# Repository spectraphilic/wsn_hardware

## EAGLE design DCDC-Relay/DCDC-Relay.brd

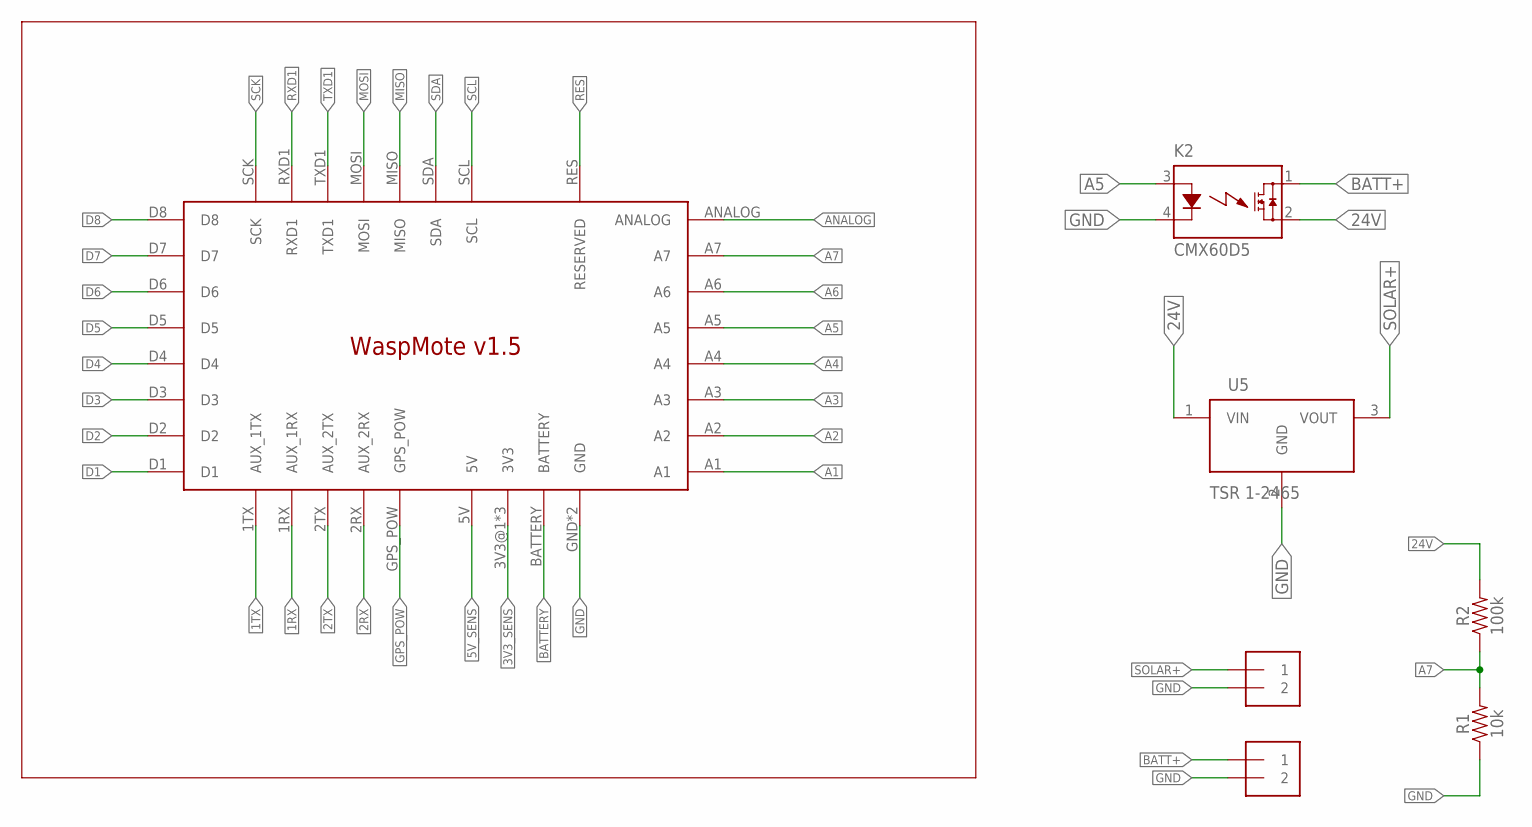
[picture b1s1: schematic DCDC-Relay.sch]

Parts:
J1, J2: 1X2-3.5MM
K2: CMX60D5
R1: 10k; AXIAL-0.3
R2: 100k; AXIAL-0.3
U5: TSR 1-2465; 173010535
U$1: WASPMOTE_V1.5

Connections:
1RX: U$1.1RX (AUX_1RX)
1TX: U$1.1TX (AUX_1TX)
2RX: U$1.2RX (AUX_2RX)
2TX: U$1.2TX (AUX_2TX)
3V3_SENS: U$1.3V3@1 (3V3), U$1.3V3@2 (3V3), U$1.3V3@3 (3V3)
5V_SENS: U$1.5V
24V: K2.2 (DS2), R2.P$2 (2), U5.1 (VIN)
A1: U$1.A1
A2: U$1.A2
A3: U$1.A3
A4: U$1.A4
A5: K2.3 (A), U$1.A5
A6: U$1.A6
A7: R1.P$2 (2), R2.P$1 (1), U$1.A7
ANALOG: U$1.ANALOG
BATT+: J1.1, K2.1 (DS1)
BATTERY: U$1.BATTERY
D1: U$1.D1
D2: U$1.D2
D3: U$1.D3
D4: U$1.D4
D5: U$1.D5
D6: U$1.D6
D7: U$1.D7
D8: U$1.D8
GND: J1.2, J2.2, K2.4 (K), R1.P$1 (1), U5.2 (GND), U$1.GND, U$1.GND_2 (GND)
GPS_POW: U$1.GPS_POW
MISO: U$1.MISO
MOSI: U$1.MOSI
RES: U$1.RES (RESERVED)
RXD1: U$1.RXD1
SCK: U$1.SCK
SCL: U$1.SCL
SDA: U$1.SDA
SOLAR+: J2.1, U5.3 (VOUT)
TXD1: U$1.TXD1

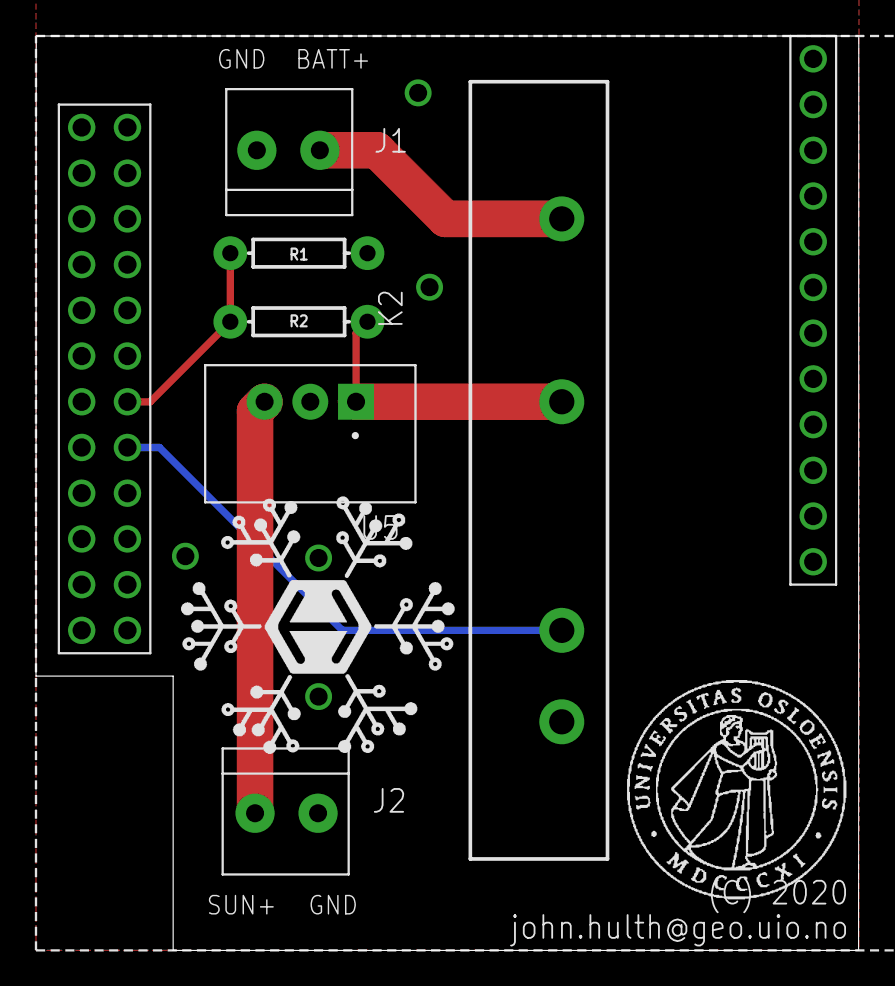
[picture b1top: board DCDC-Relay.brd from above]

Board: 2 copper layers, 45.7 x 50.8 mm, 9 parts (0 on the bottom side), 7 nets.

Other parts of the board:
U$2: HIVE-LOGO
U$3: UIO-LOGO-BL

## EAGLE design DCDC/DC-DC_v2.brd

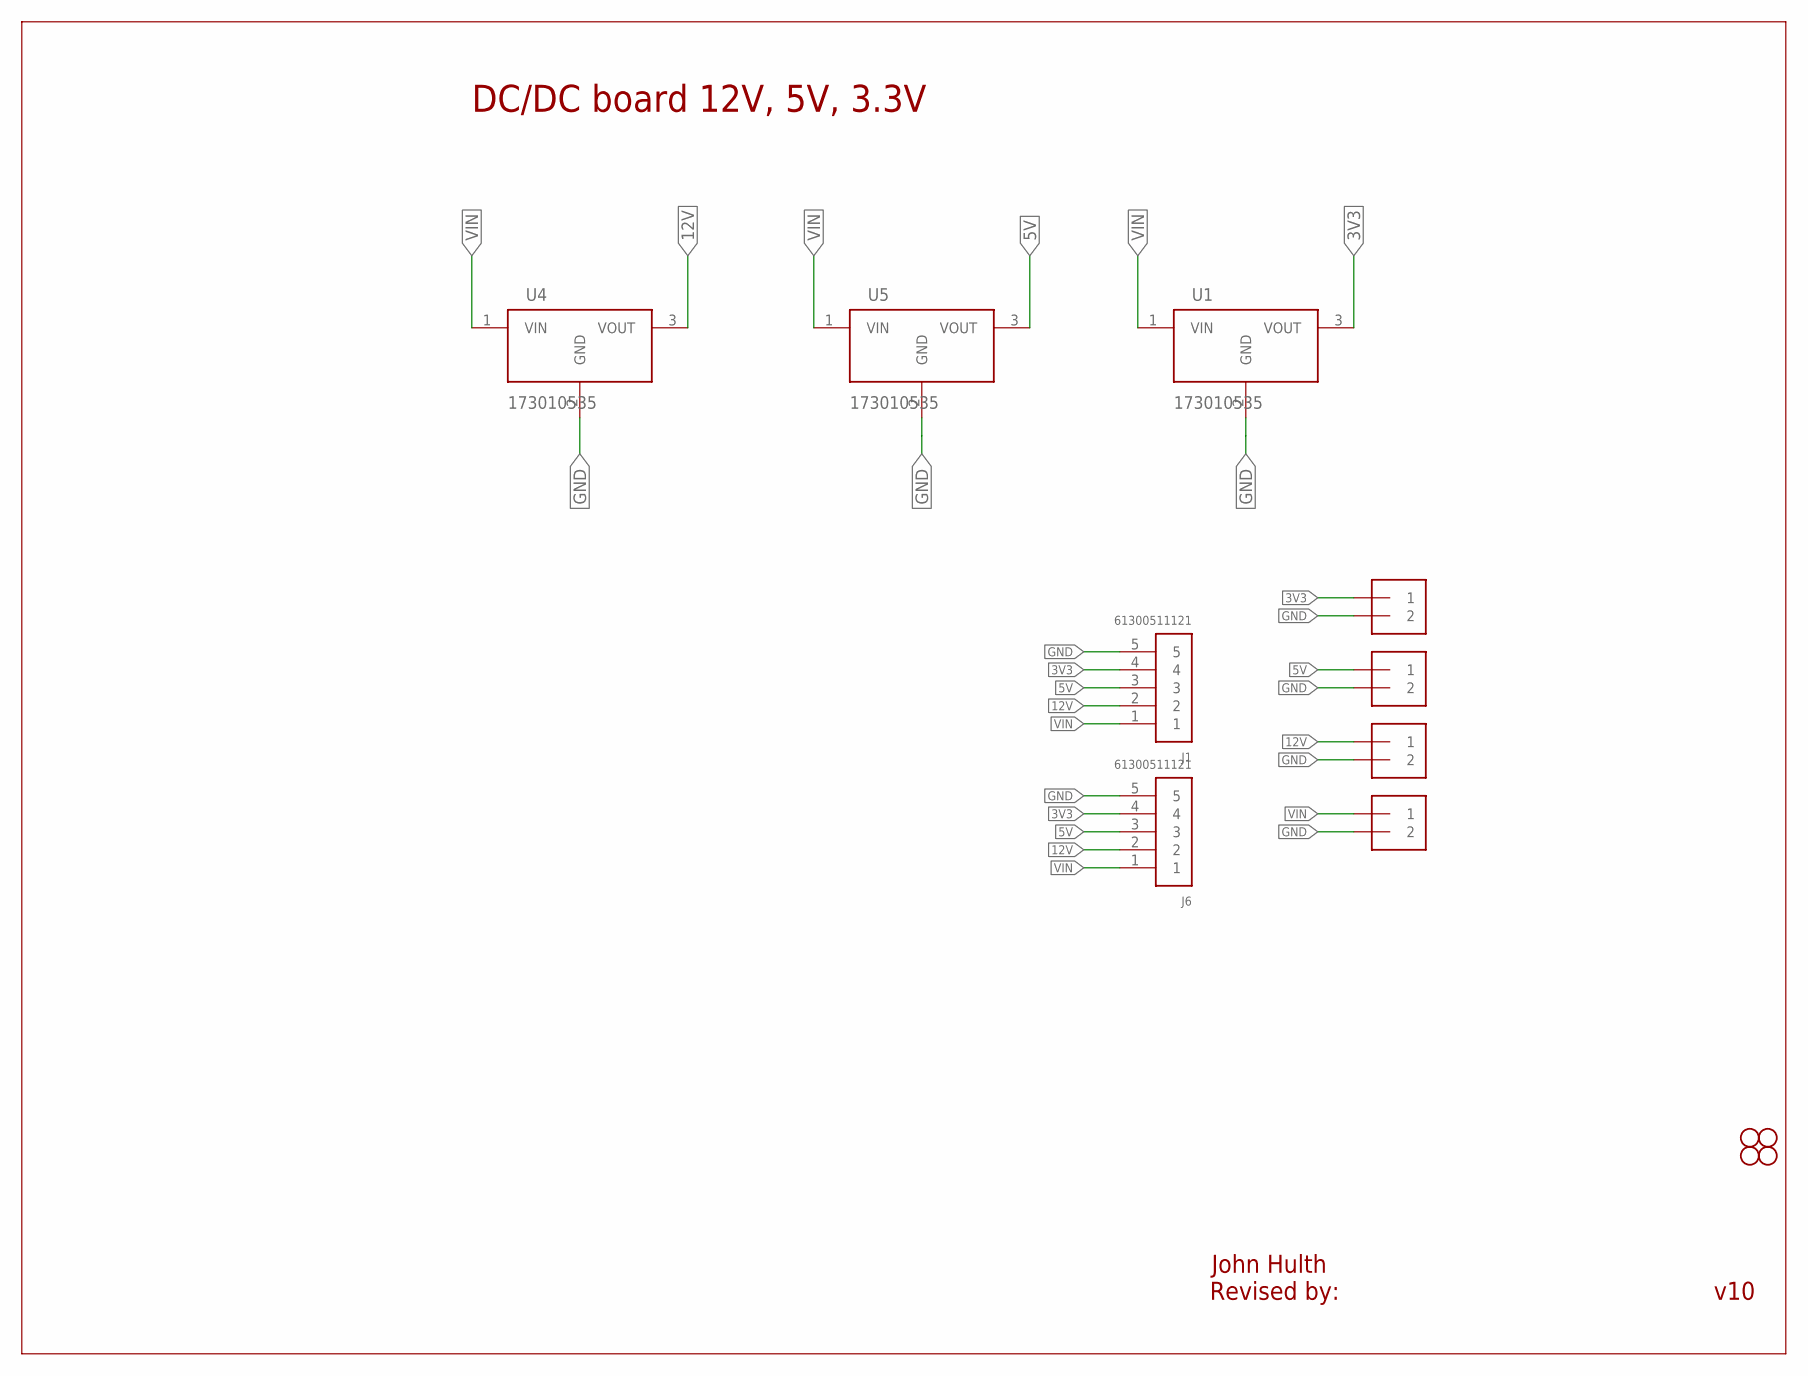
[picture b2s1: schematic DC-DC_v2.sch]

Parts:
J1, J6: 61300511121
J2, J3, J4, J5: 1X2-3.5MM
JP2, JP3, JP8, JP9: STAND-OFF
U1, U4, U5: 173010535

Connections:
3V3: J1.4, J2.1, J6.4, U1.3 (VOUT)
5V: J1.3, J3.1, J6.3, U5.3 (VOUT)
12V: J1.2, J4.1, J6.2, U4.3 (VOUT)
GND: J1.5, J2.2, J3.2, J4.2, J5.2, J6.5, U1.2 (GND), U4.2 (GND), U5.2 (GND)
VIN: J1.1, J5.1, J6.1, U1.1 (VIN), U4.1 (VIN), U5.1 (VIN)

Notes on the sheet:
DC/DC board 12V, 5V, 3.3V
John Hulth
v10
Revised by:

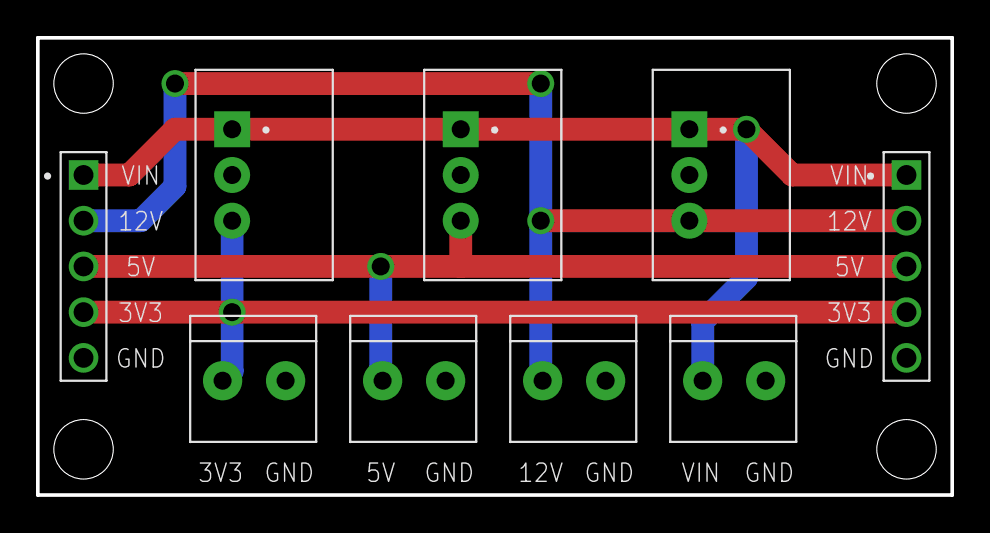
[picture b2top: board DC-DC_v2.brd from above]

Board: 2 copper layers, 50.8 x 25.4 mm, 14 parts (1 on the bottom side), 5 nets.

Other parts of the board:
U$3: UIO-LOGO-BL

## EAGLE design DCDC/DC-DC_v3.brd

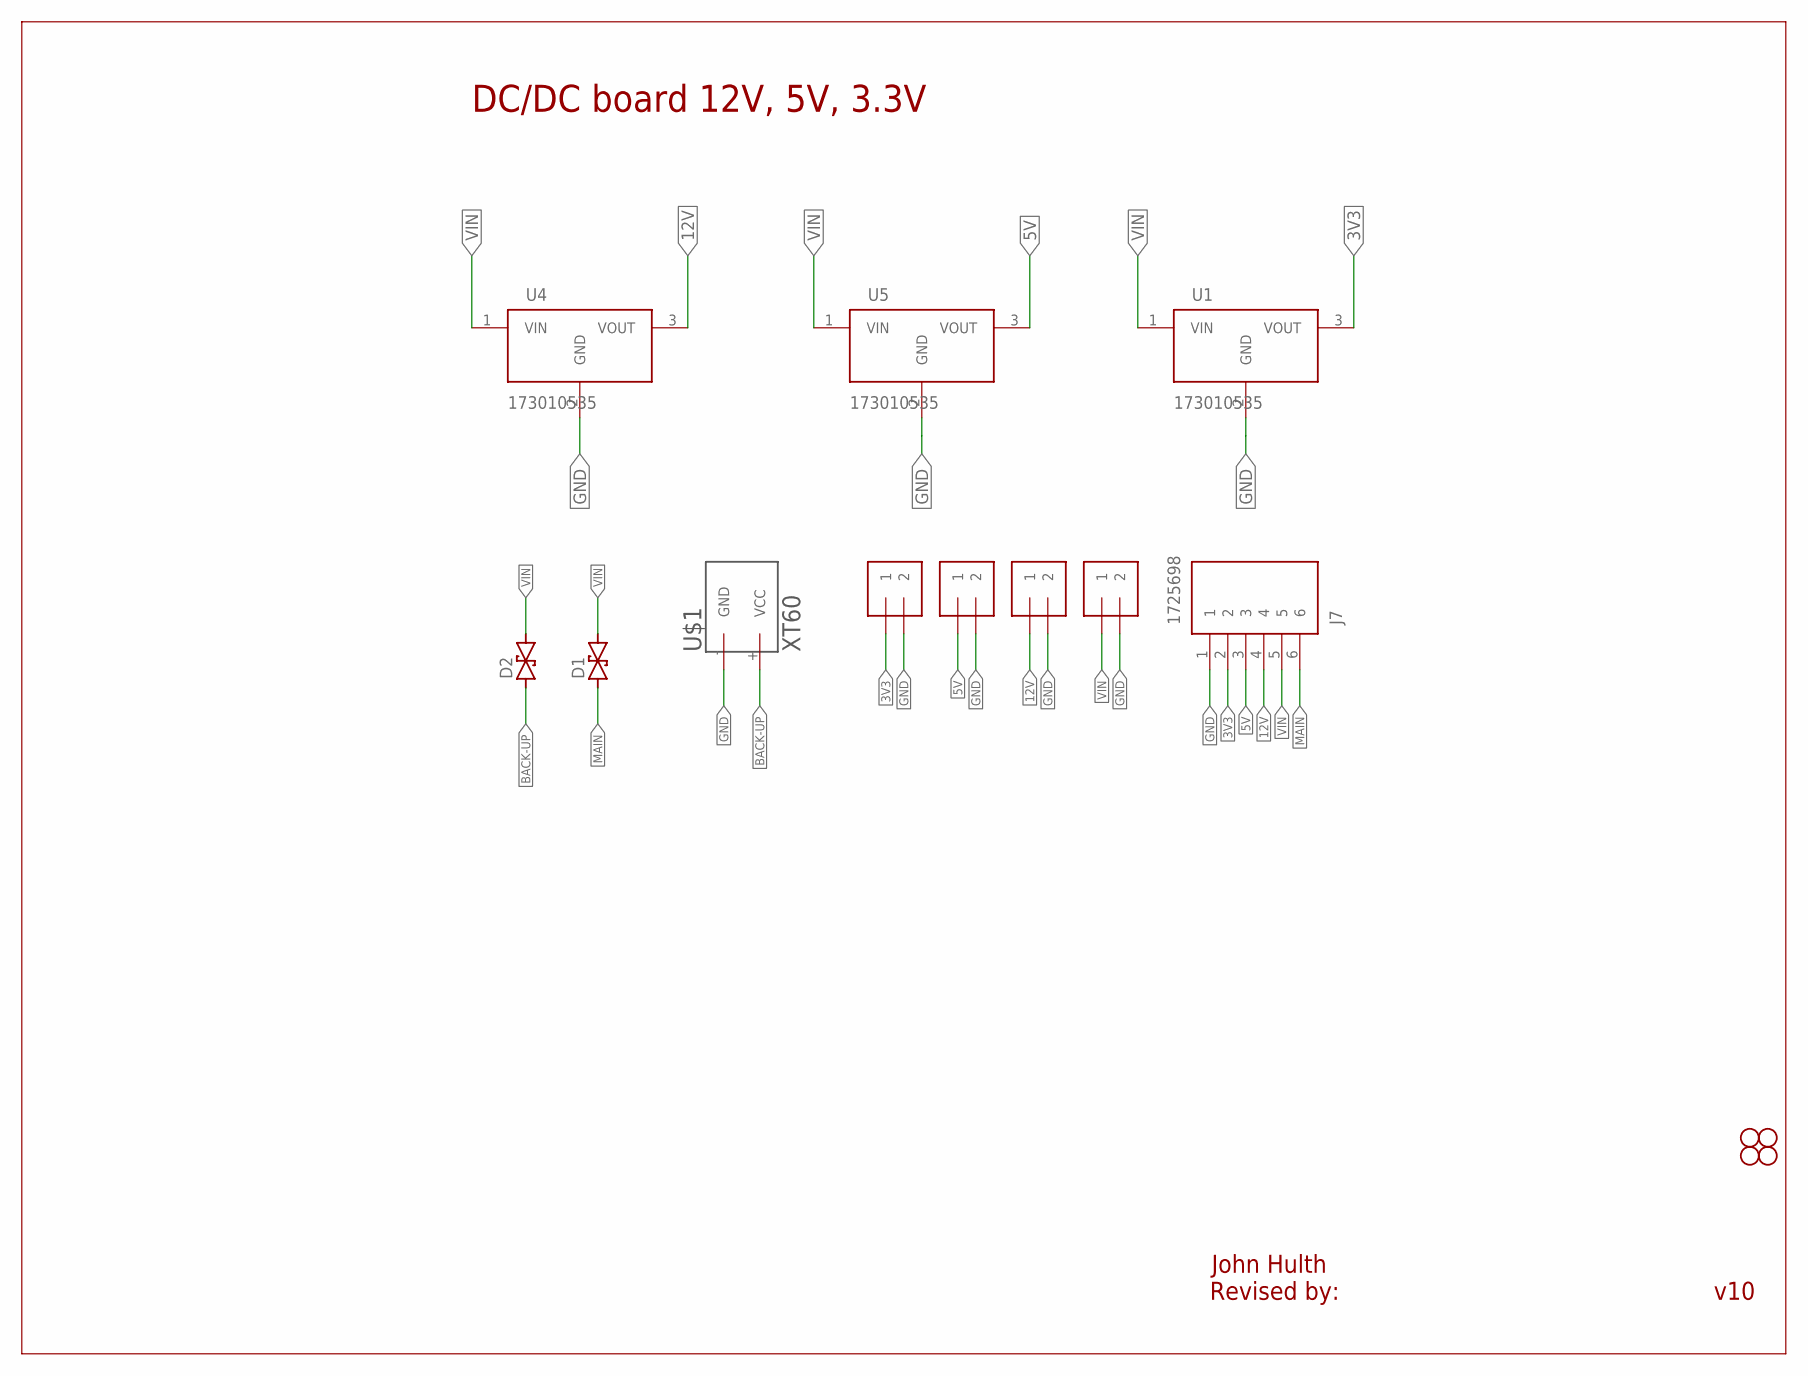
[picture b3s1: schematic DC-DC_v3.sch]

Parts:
D1, D2: DIODE_SCHOTTKY2-P2-15; P2-15
J2, J3, J4, J5: 1X2-3.5MM
J7: 1725698; SHDR6W90P0X254_1X6_1570X620X85
JP2, JP3, JP8, JP9: STAND-OFF
U1, U4, U5: 173010535
U$1: XT60

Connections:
3V3: J2.1, J7.2, U1.3 (VOUT)
5V: J3.1, J7.3, U5.3 (VOUT)
12V: J4.1, J7.4, U4.3 (VOUT)
BACK-UP: D2.A (1), U$1.+ (VCC)
GND: J2.2, J3.2, J4.2, J5.2, J7.1, U1.2 (GND), U4.2 (GND), U5.2 (GND), U$1.- (GND)
MAIN: D1.A (1), J7.6
VIN: D1.C (2), D2.C (2), J5.1, J7.5, U1.1 (VIN), U4.1 (VIN), U5.1 (VIN)

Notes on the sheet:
DC/DC board 12V, 5V, 3.3V
John Hulth
v10
Revised by:

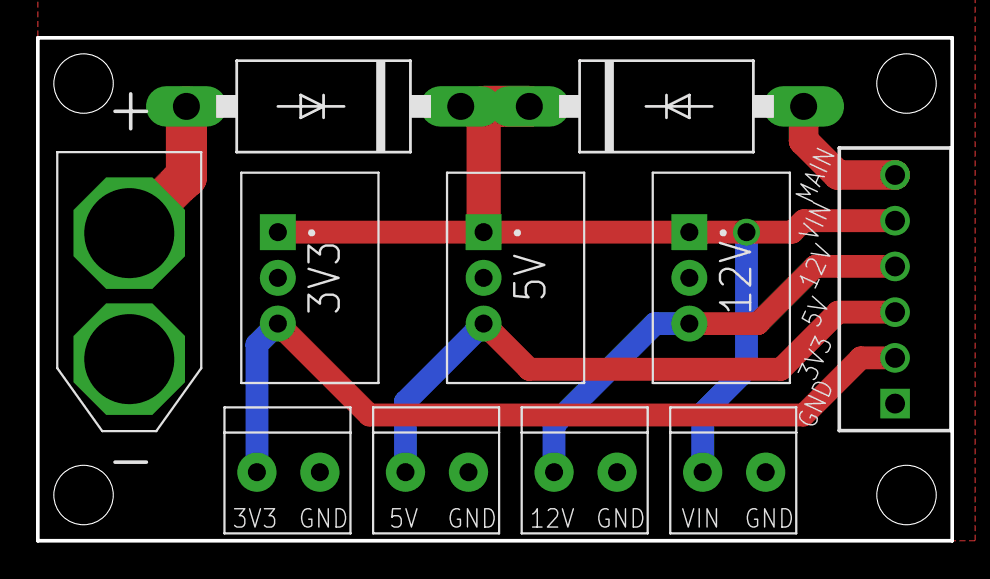
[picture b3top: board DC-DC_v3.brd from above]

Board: 2 copper layers, 50.8 x 27.9 mm, 16 parts (1 on the bottom side), 7 nets.

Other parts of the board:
U$3: UIO-LOGO-BL

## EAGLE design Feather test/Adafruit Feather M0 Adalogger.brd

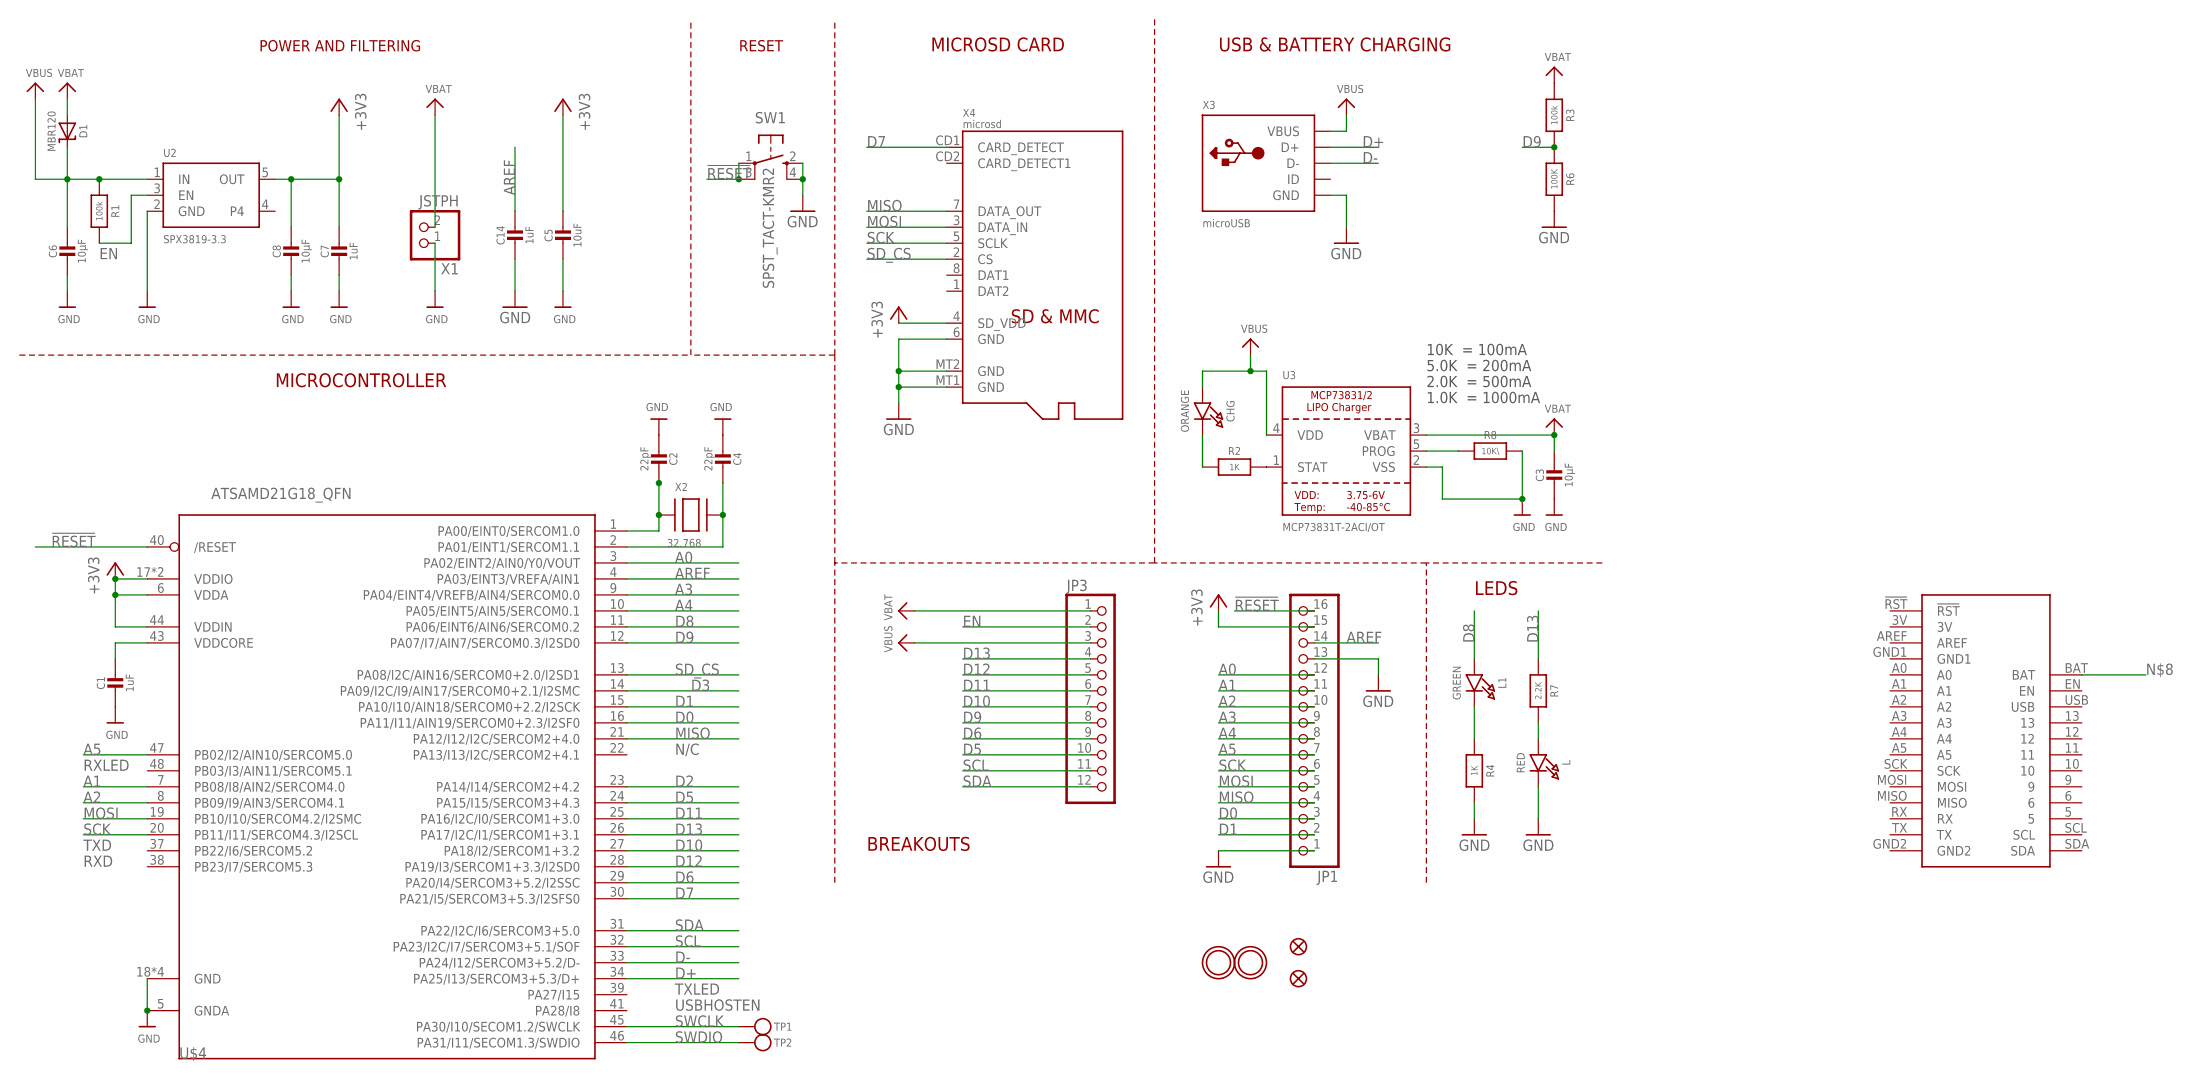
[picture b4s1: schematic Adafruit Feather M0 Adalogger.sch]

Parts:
C1, C7, C14: 1uF; 0603-NO
C2, C4: 22pF; 0603-NO
C3, C6, C8: 10µF; 0805-NO
C5: 10uF; 0805-NO
CHG: ORANGE; CHIPLED_0805_NOOUTLINE
D1: MBR120; SOD-123
JP1: HEADER-1X16ROUND; 1X16_ROUND
JP3: HEADER-1X12; 1X12_ROUND
L: RED; CHIPLED_0805_NOOUTLINE
L1: GREEN; CHIPLED_0805_NOOUTLINE
R1, R3: 100k; 0603-NO
R2, R4: 1K; 0603-NO
R6: 100K; 0603-NO
R7: 2.2K; 0603-NO
R8: 10K\; 0603-NO
SW1: SPST_TACT-KMR2; KMR2
TP1, TP2: TESTPOINTROUND1.5MM; TESTPOINT_ROUND_1.5MM
U2: SPX3819-3.3; SOT23-5
U3: MCP73831T-2ACI/OT; SOT23-5
U$4: ATSAMD21G18_QFN; TQFN48_7MM
U$12: FEATHER_MO_ADALOGGER; FEATHER_M0_ADALOGGER
U$31, U$32: MOUNTINGHOLE2.5; MOUNTINGHOLE_2.5_PLATED
U$34, U$35: FIDUCIAL""; FIDUCIAL_1MM
X1: JSTPH; JSTPH2
X2: 32.768; XTAL3215
X3: microUSB; 4UCONN_20329_V2
X4: microsd; MICROSD

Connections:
!RESET: JP1.16, SW1.1, SW1.3 (P1), U$4.40 (/RESET)
+3V3: C5.1, C7.1, C8.1, JP1.15, U2.5 (OUT), U$4.6 (VDDA), U$4.17 (VDDIO), U$4.36 (VDDIO), U$4.44 (VDDIN), X4.4 (SD_VDD)
A0: JP1.12, U$4.3 (PA02/EINT2/AIN0/Y0/VOUT)
A1: JP1.11, U$4.7 (PB08/I8/AIN2/SERCOM4.0)
A2: JP1.10, U$4.8 (PB09/I9/AIN3/SERCOM4.1)
A3: JP1.9, U$4.9 (PA04/EINT4/VREFB/AIN4/SERCOM0.0)
A4: JP1.8, U$4.10 (PA05/EINT5/AIN5/SERCOM0.1)
A5: JP1.7, U$4.47 (PB02/I2/AIN10/SERCOM5.0)
AREF: C14.1, JP1.14, U$4.4 (PA03/EINT3/VREFA/AIN1)
D0: JP1.3, U$4.16 (PA11/I11/AIN19/SERCOM0+2.3/I2SF0)
D1: JP1.2, U$4.15 (PA10/I10/AIN18/SERCOM0+2.2/I2SCK)
D2: U$4.23 (PA14/I14/SERCOM2+4.2)
D3: U$4.14 (PA09/I2C/I9/AIN17/SERCOM0+2.1/I2SMC)
D5: JP3.10, U$4.24 (PA15/I15/SERCOM3+4.3)
D6: JP3.9, U$4.29 (PA20/I4/SERCOM3+5.2/I2SSC)
D7: U$4.30 (PA21/I5/SERCOM3+5.3/I2SFS0), X4.CD1 (CARD_DETECT)
D8: L1.A, U$4.11 (PA06/EINT6/AIN6/SERCOM0.2)
D9: JP3.8, R3.2, R6.1, U$4.12 (PA07/I7/AIN7/SERCOM0.3/I2SD0)
D10: JP3.7, U$4.27 (PA18/I2/SERCOM1+3.2)
D11: JP3.6, U$4.25 (PA16/I2C/I0/SERCOM1+3.0)
D12: JP3.5, U$4.28 (PA19/I3/SERCOM1+3.3/I2SD0)
D13: JP3.4, R7.1, U$4.26 (PA17/I2C/I1/SERCOM1+3.1)
D+: U$4.34 (PA25/I13/SERCOM3+5.3/D+), X3.D+
D-: U$4.33 (PA24/I12/SERCOM3+5.2/D-), X3.D-
EN: JP3.2, R1.2, U2.3 (EN)
GND: C1.2, C2.2, C3.2, C4.2, C5.2, C6.2, C7.2, C8.2, C14.2, JP1.1, JP1.13, L.C, R4.2, R6.2, R8.2, SW1.2 (S), SW1.4 (S1), U2.2 (GND), U3.2 (VSS), U$4.5 (GNDA), U$4.18 (GND), U$4.35 (GND), U$4.42 (GND), U$4.THERMAL (GND), X1.1, X3.BASE@1 (GND), X3.BASE@2 (GND), X3.GND, X3.SPRT@1 (GND), X3.SPRT@2 (GND), X3.SPRT@3 (GND), X3.SPRT@4 (GND), X4.6 (GND), X4.MT1 (GND), X4.MT2 (GND)
MISO: JP1.4, U$4.21 (PA12/I12/I2C/SERCOM2+4.0), X4.7 (DATA_OUT)
MOSI: JP1.5, U$4.19 (PB10/I10/SERCOM4.2/I2SMC), X4.3 (DATA_IN)
unnamed: CHG.C, R2.1
unnamed: L.A, R7.2
unnamed: R2.2, U3.1 (STAT)
unnamed: R8.1, U3.5 (PROG)
unnamed: C2.1, U$4.1 (PA00/EINT0/SERCOM1.0), X2.P$1
unnamed: L1.C, R4.1
unnamed: C4.1, U$4.2 (PA01/EINT1/SERCOM1.1), X2.P$2
SCK: JP1.6, U$4.20 (PB11/I11/SERCOM4.3/I2SCL), X4.5 (SCLK)
SCL: JP3.11, U$4.32 (PA23/I2C/I7/SERCOM3+5.1/SOF)
SDA: JP3.12, U$4.31 (PA22/I2C/I6/SERCOM3+5.0)
SD_CS: U$4.13 (PA08/I2C/AIN16/SERCOM0+2.0/I2SD1), X4.2 (CS)
SWCLK: TP1.P$1, U$4.45 (PA30/I10/SECOM1.2/SWCLK)
SWDIO: TP2.P$1, U$4.46 (PA31/I11/SECOM1.3/SWDIO)
VBAT: C3.1, D1.A, JP3.1, R3.1, U3.3 (VBAT), X1.2
VBUS: C6.1, CHG.A, D1.C, JP3.3, R1.1, U2.1 (IN), U3.4 (VDD), X3.VBUS
VDDCORE: C1.1, U$4.43 (VDDCORE)

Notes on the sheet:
POWER AND FILTERING
RESET
10K = 100mA
5.0K = 200mA
2.0K = 500mA
1.0K = 1000mA
N/C
TXLED
USBHOSTEN
RXLED
TXD
RXD
USB & BATTERY CHARGING
MICROSD CARD
BREAKOUTS
LEDS
MICROCONTROLLER

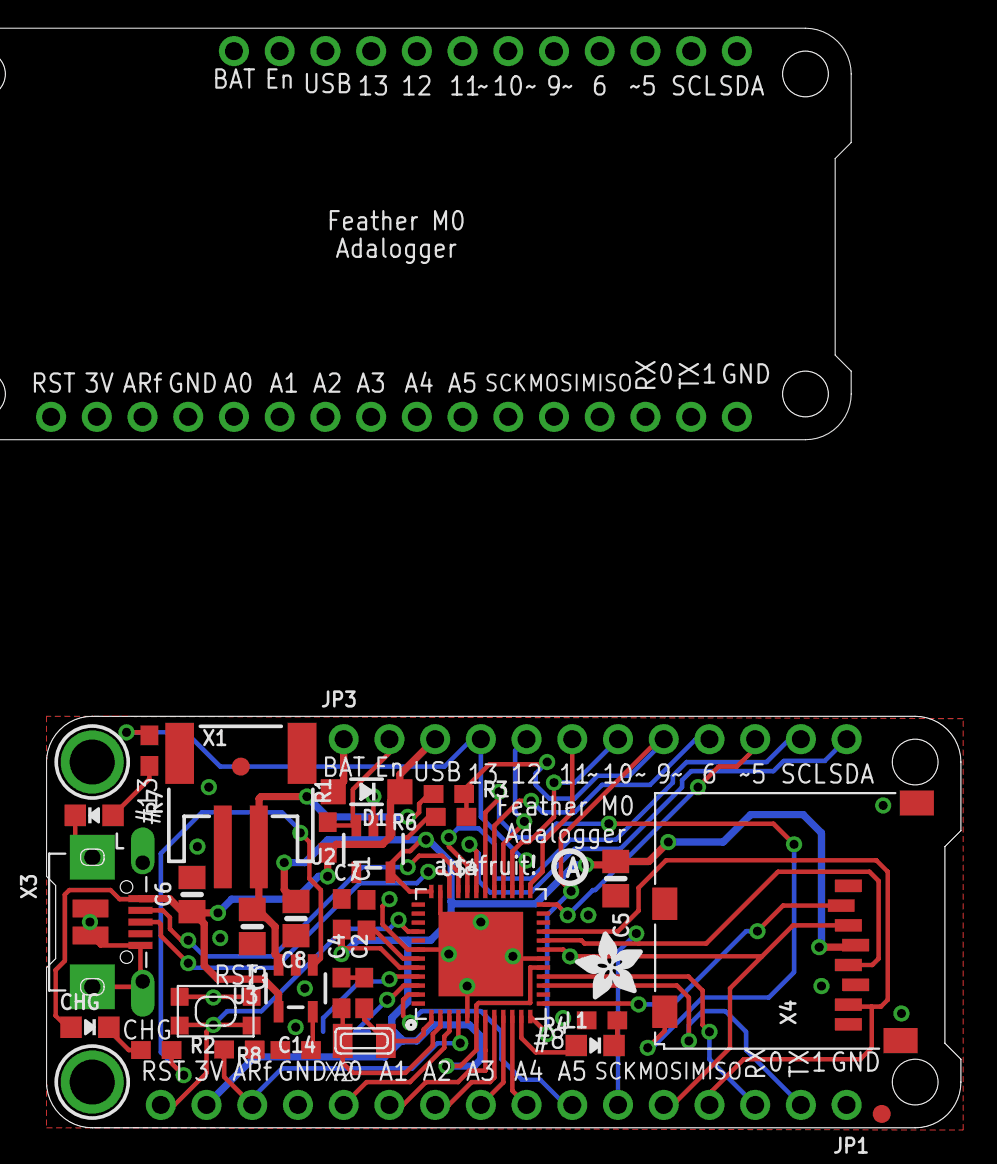
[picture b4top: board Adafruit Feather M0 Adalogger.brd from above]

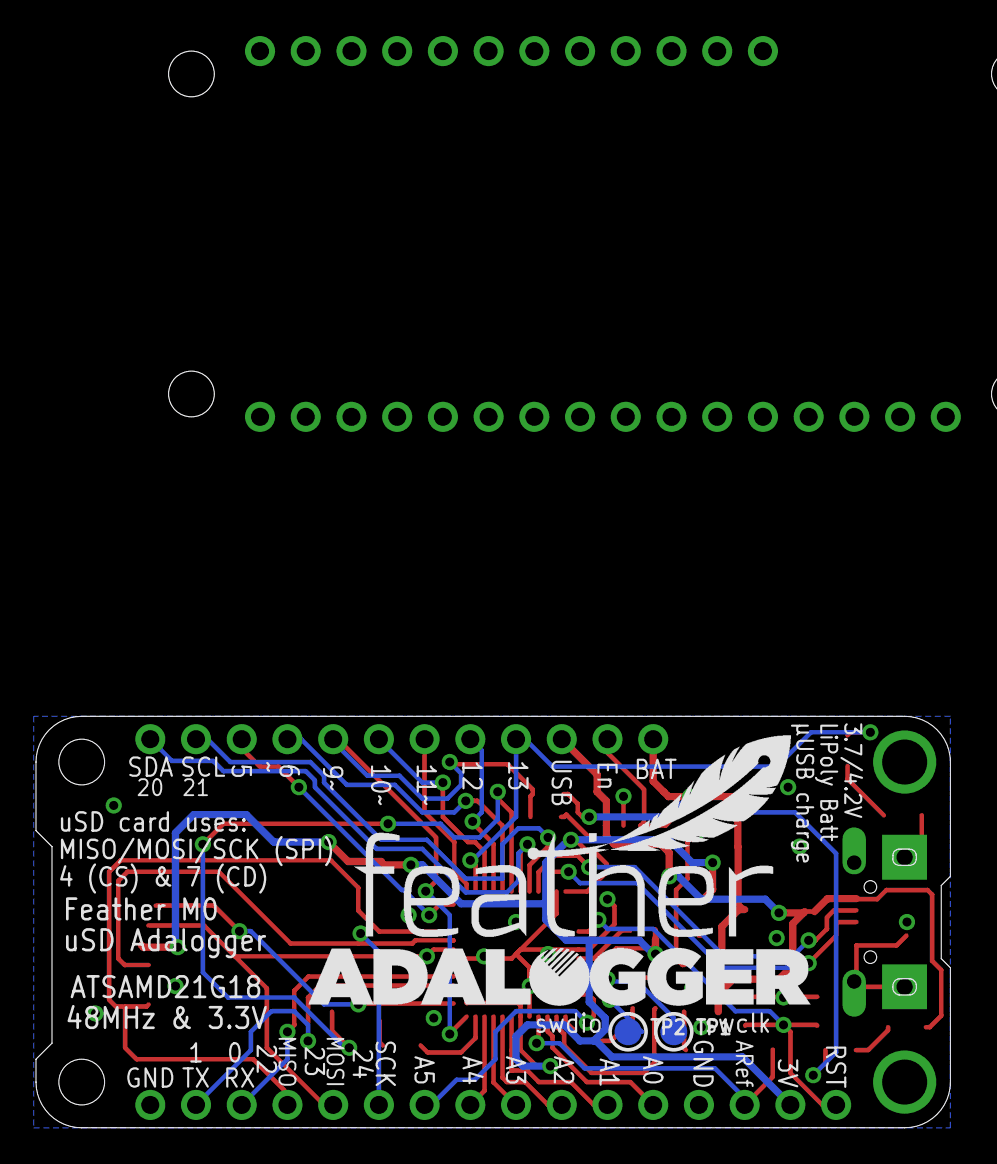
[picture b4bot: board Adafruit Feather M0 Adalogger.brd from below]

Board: 2 copper layers, 50.8 x 22.9 mm, 41 parts (4 on the bottom side), 42 nets.

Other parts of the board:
U$7: ADAFRUIT_3.5MM
U$9: PCBFEAT-REV-040
U$13: FEATHERLOGO
U$14: ADALOGGER_LOGO

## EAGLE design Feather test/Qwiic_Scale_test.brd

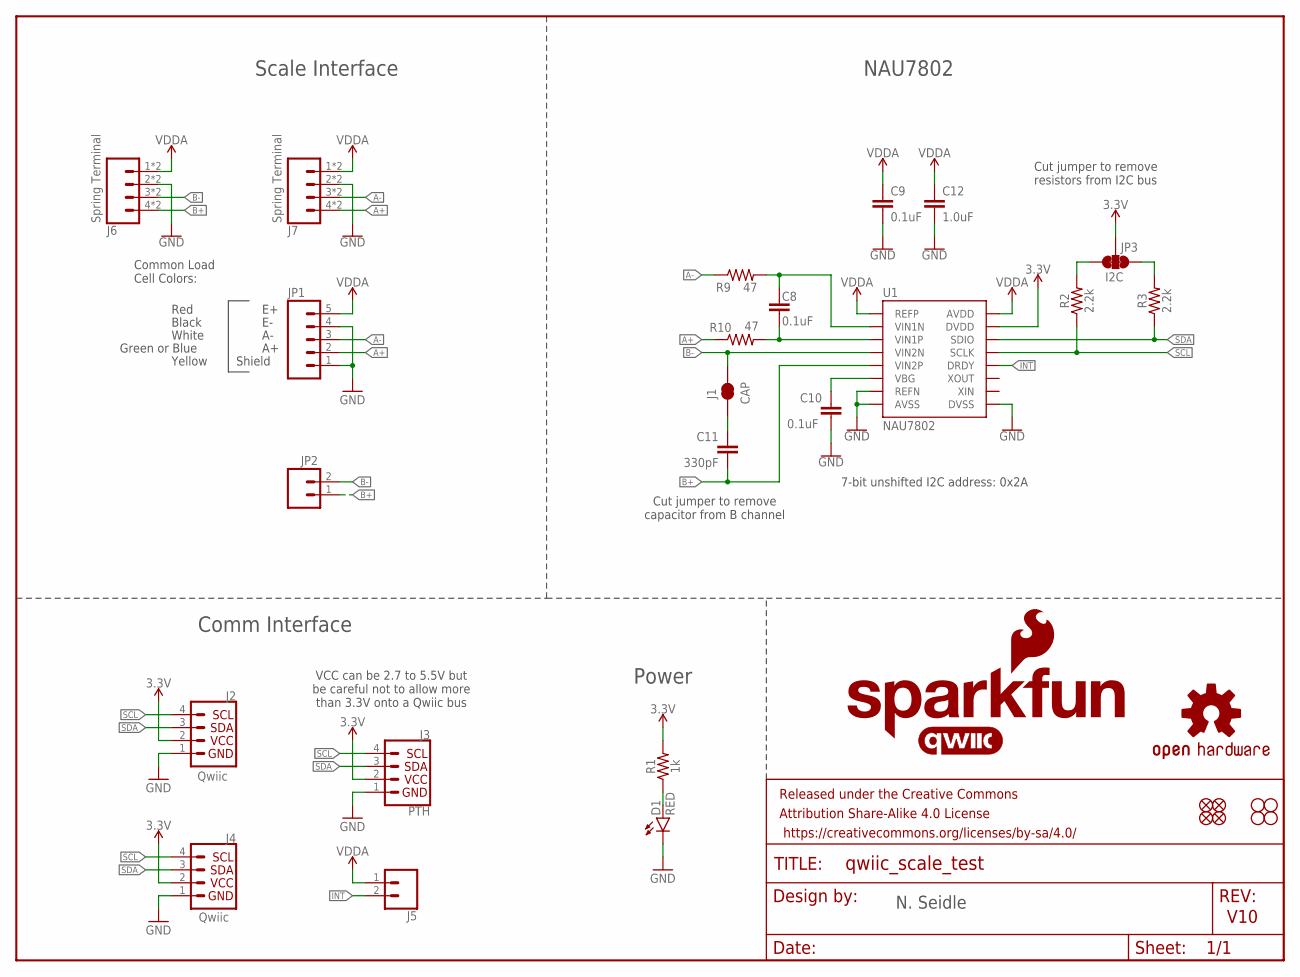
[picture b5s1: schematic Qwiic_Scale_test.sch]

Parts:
C8, C9, C10: 0.1uF; 0603
C11: 330pF; 0603
C12: 1.0uF; 0603
D1: RED; LED-0603
FRAME1: FRAME-LETTER; CREATIVE_COMMONS
J1: CAP; SMT-JUMPER_2_NC_TRACE_SILK
J2, J4: Qwiic; JST04_1MM_RA
J3: PTH; 1X04_NO_SILK
J5: CONN_021X02_NO_SILK; 1X02_NO_SILK
J6, J7: Spring Terminal; 1X04_SPRING_TERMINAL
JP1: CONN_05NO_SILK; 1X05_NO_SILK
JP2: CONN_021X02_NO_SILK; 1X02_NO_SILK
JP3: I2C; SMT-JUMPER_3_2-NC_TRACE_SILK
JP21, JP61, JP71, JP81: FIDUCIALUFIDUCIAL; MICRO-FIDUCIAL
JP31, JP41, JP91, JP101: STAND-OFF
LOGO1: OSHW-LOGOMINI; OSHW-LOGO-MINI
LOGO2: SFE_LOGO_NAME_FLAME.1_INCH; SFE_LOGO_NAME_FLAME_.1
R1: 1k; 0603
R2, R3: 2.2k; 0603
R9, R10: 47; 0603
U1: NAU7802; SO16
U$16: QWIIC_LOGO_7MM; QWIIC_7MM

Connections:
3.3V: J2.2, J3.2, J4.2, JP3.2, R1.2, U1.15 (DVDD)
A+: J7.4, J7.8 (4), JP1.2, R10.1
A-: J7.3, J7.7 (3), JP1.3, R9.1
B+: C11.2, J6.4, J6.8 (4), JP2.1, U1.5 (VIN2P)
B-: J1.2, J6.3, J6.7 (3), JP2.2, U1.4 (VIN2N)
GND: C9.2, C10.2, C12.2, D1.C, J2.1, J3.1, J4.1, J6.2, J6.6 (2), J7.2, J7.6 (2), JP1.1, JP1.4, U1.7 (REFN), U1.8 (AVSS), U1.9 (DVSS)
INT: J5.2, U1.12 (DRDY)
unnamed: C11.1, J1.1
unnamed: JP3.1, R3.2
unnamed: JP3.3, R2.2
unnamed: D1.A, R1.1
unnamed: C10.1, U1.6 (VBG)
unnamed: C8.2, R10.2, U1.3 (VIN1P)
unnamed: C8.1, R9.2, U1.2 (VIN1N)
SCL: J2.4, J3.4, J4.4, R2.1, U1.13 (SCLK)
SDA: J2.3, J3.3, J4.3, R3.1, U1.14 (SDIO)
VDDA: C9.1, C12.1, J5.1, J6.1, J6.5 (1), J7.1, J7.5 (1), JP1.5, U1.1 (REFP), U1.16 (AVDD)

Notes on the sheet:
V10
7-bit unshifted I2C address: 0x2A
Cut jumper to remove resistors from I2C bus
Red
Black
White
Green or Blue
Common Load Cell Colors:
Shield
Yellow
Cut jumper to remove capacitor from B channel
N. Seidle
NAU7802
Comm Interface
Scale Interface
Power
VCC can be 2.7 to 5.5V but be careful not to allow more than 3.3V onto a Qwiic bus

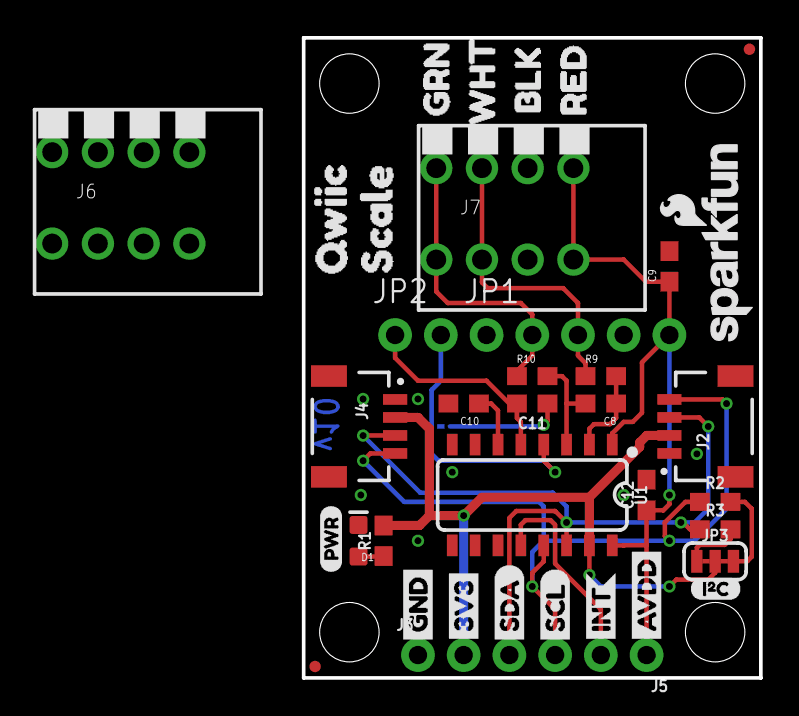
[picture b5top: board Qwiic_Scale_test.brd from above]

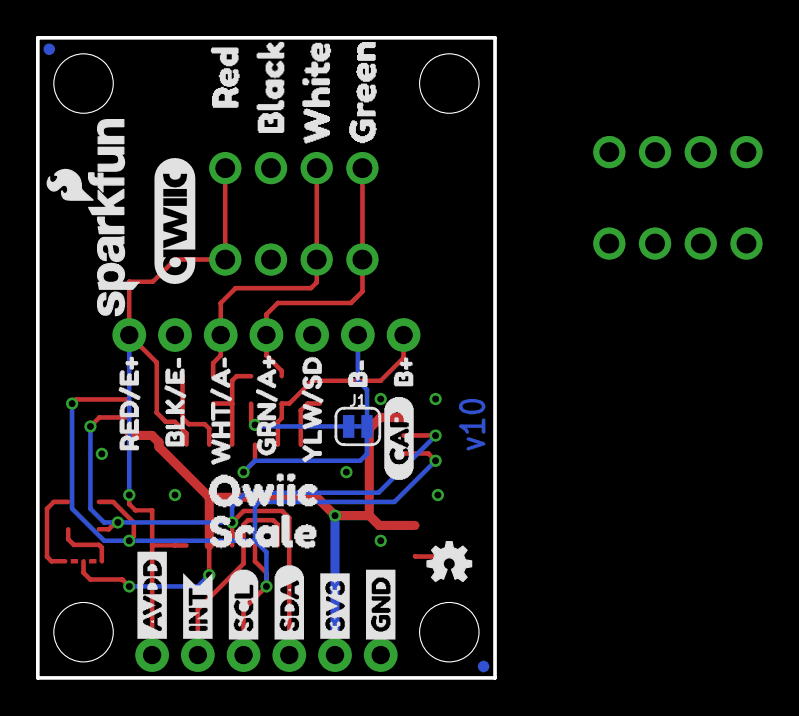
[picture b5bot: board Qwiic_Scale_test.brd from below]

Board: 2 copper layers, 25.4 x 35.6 mm, 69 parts (26 on the bottom side), 17 nets.

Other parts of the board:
LOGO3: SFE_LOGO_NAME_FLAME.1_INCH; SFE_LOGO_NAME_FLAME_.1
U$1, U$4: SDA-[)
U$3, U$5: SCL-[)
U$6, U$7: 3V3-04
U$8, U$9: GND-04
U$11: YLW#SD4
U$12: B#11
U$13: B#12
U$14, U$22: QWIIC2
U$15, U$21: INT0
U$17, U$24: SCALE3
U$18: PWR-()-03
U$19: I_SUPER2_C-()-03
U$20: CAP0
U$34: BLK#E#1
U$35: GRN#A#4
U$36, U$45: AVDD4
U$37: BLACK5
U$38: BLK1
U$39: GREEN7
U$40: GRN3
U$41: RED0
U$42: RED4
U$43: WHITE6
U$44: WHT2
U$46: RED#E#2
U$48: WHT#A#3

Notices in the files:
DCDC-Relay/DCDC-Relay.brd:
(C) 2020
DCDC/DC-DC_v3.brd:
(C) 2021
parts and their libraries:
UIO-John: (c) 2017 john.hulth@geo.uio.no
SparkFun-Resistors: Licensing: Creative Commons ShareAlike 4.0 International - https://creativecommons.org/licenses/by-sa/4.0
SparkFun-Aesthetics: Released under the Creative Commons Attribution Share-Alike 4.0 License
